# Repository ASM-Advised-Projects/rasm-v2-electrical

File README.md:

Repository for all RASM electronics files. This is mainly comprised of schematics, printed circuit boards, and some custom component libraries.

The images folder which will contain screenshots of the current schematics and boards so that you don't have to have eagle just to get an overview of everything.

Resources for starting to learn how to use Eagle:
* http://eagle.autodesk.com/eagle/documentation
* https://www.autodesk.com/products/eagle/blog/?s=library
* general internetz

Some other tools:
* Trace width calculator: http://circuitcalculator.com/wordpress/?p=25/
* Via dimensions calculator: http://circuitcalculator.com/wordpress/2006/03/12/pcb-via-calculator/

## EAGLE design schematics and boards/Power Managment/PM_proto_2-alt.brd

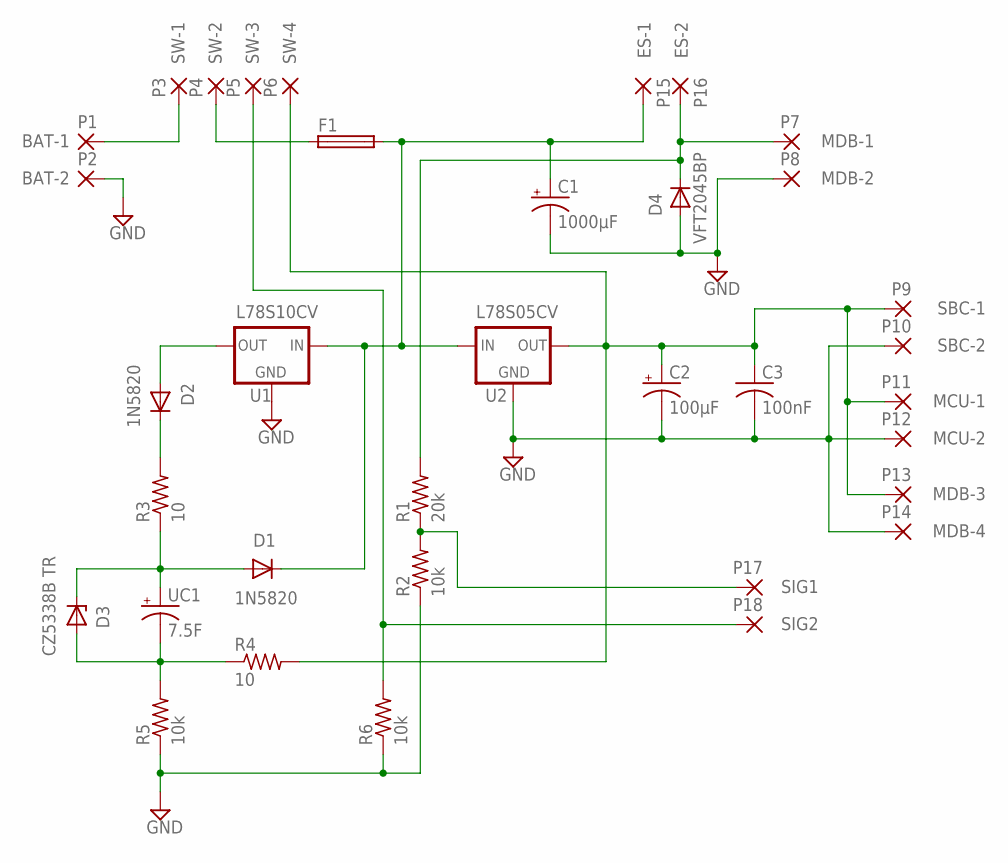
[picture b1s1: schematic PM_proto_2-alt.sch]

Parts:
C1: 1000μF; E7,5-16
C2: 100μF; E2,5-6E
C3: 100nF; C050-024X044
D1, D2: 1N5820; DO41-10
D3: CZ5338B TR; DO41Z10
D4: VFT2045BP
F1: 0297015FUSE; 0297015HOLDER
P1: BAT-1; 1,6/0,8
P2: BAT-2; 1,6/0,8
P3: SW-1; 1,6/0,8
P4: SW-2; 1,6/0,8
P5: SW-3; 1,6/0,8
P6: SW-4; 1,6/0,8
P7: MDB-1; 1,6/0,8
P8: MDB-2; 1,6/0,8
P9: SBC-1; 1,6/0,8
P10: SBC-2; 1,6/0,8
P11: MCU-1; 1,6/0,8
P12: MCU-2; 1,6/0,8
P13: MDB-3; 1,6/0,8
P14: MDB-4; 1,6/0,8
P15: ES-1; 1,6/0,8
P16: ES-2; 1,6/0,8
P17: SIG1; 1,6/0,8
P18: SIG2; 1,6/0,8
R1: 20k; 0204/7
R2, R5, R6: 10k; 0204/7
R3, R4: 10; TNP10SC10R0FE
U1: L78S10CV; 78XXS
U2: L78S05CV; 78XXS
UC1: 7.5F; SCMT32D755MRBB0

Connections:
5VPWR: C2.+, C3.1, P6.1, P9.1, P11.1, P13.1, R4.2, U2.OUT
BATT_1: P1.1, P3.1
BATT_2: F1.1, F1.2 (1), P4.1
BATT_3: C1.+, D1.C, F1.3 (2), F1.4 (2), P15.1, U1.IN, U2.IN
BATT_4: D4.1 (C), P7.1, P16.1, R1.2
CAP_NEG: D3.A, R4.1, R5.2, UC1.2 (-)
CAP_POS: D1.A, D3.C, R3.1, UC1.1 (+)
GND: C1.-, C2.-, C3.2, D4.2 (A), P2.1, P8.1, P10.1, P12.1, P14.1, R2.1, R5.1, R6.1, U1.GND, U2.GND
unnamed: D2.A, U1.OUT
unnamed: D2.C, R3.2
ON_SENSE: P5.1, P18.1, R6.2
V_SENSE: P17.1, R1.1, R2.2

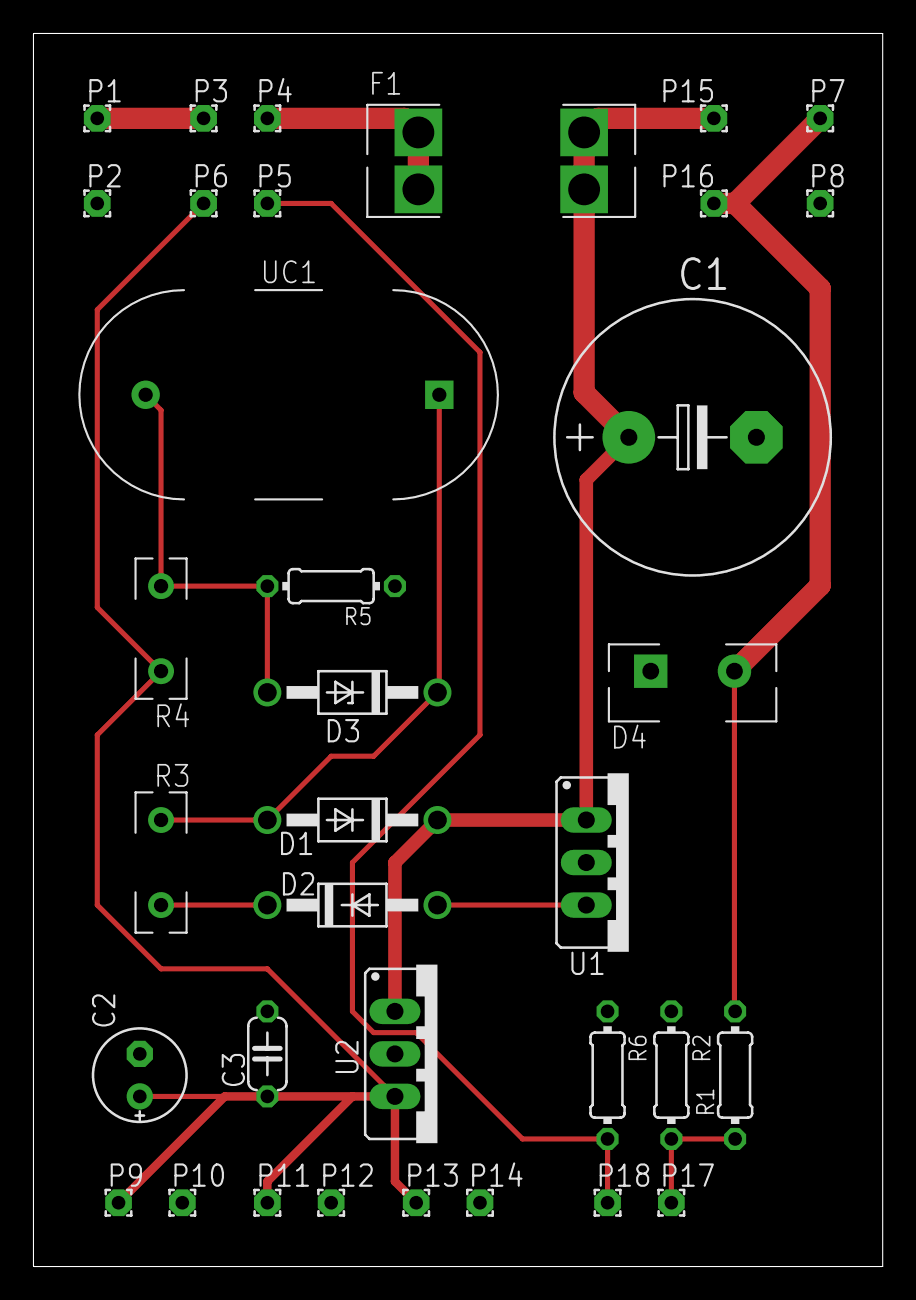
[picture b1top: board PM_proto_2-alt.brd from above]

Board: 2 copper layers, 50.7 x 73.7 mm, 35 parts (0 on the bottom side), 12 nets.

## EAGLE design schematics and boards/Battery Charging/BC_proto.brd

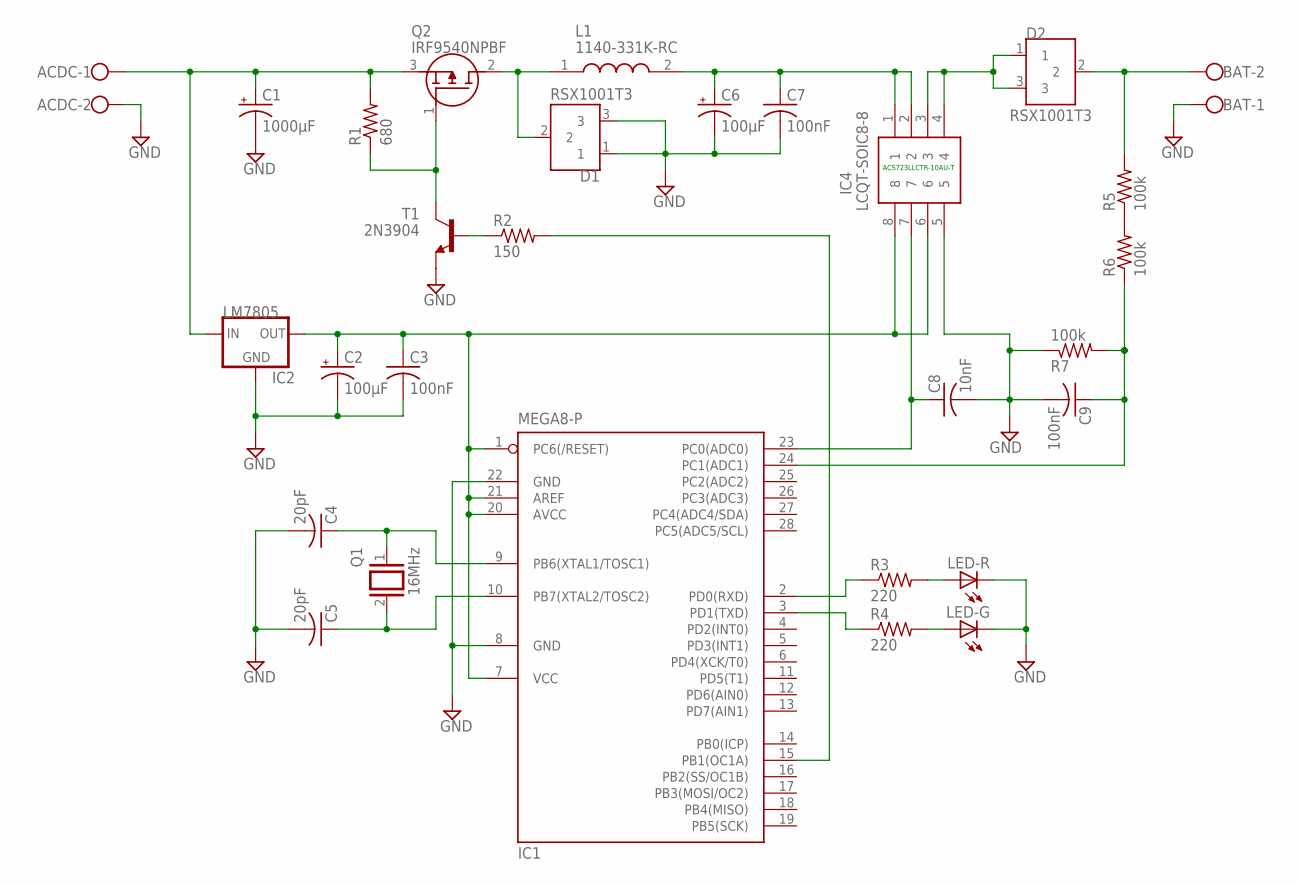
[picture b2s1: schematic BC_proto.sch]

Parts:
ACDC: W237-102
BAT: W237-102
C1: 1000μF; E7,5-16
C2, C6: 100μF; E2,5-6E
C3, C7, C9: 100nF; C050-024X044
C4, C5: 20pF; C050-024X044
C8: 10nF; C050-024X044
D1, D2: RSX1001T3
IC1: MEGA8-P; DIL28-3
IC2: LM7805; 78XXS
IC4: LCQT-SOIC8-8; DIPS762W46P254L1016H160Q8N
L1: 1140-331K-RC
LED-G: TLLR4400; LED3MM
LED-R: TLLR4400; LED3MM
Q1: 16MHz; QS
Q2: IRF9540NPBF; TO254P469X1042X1967-3P
R1: 680; 0204/7
R2: 150; 0204/7
R3, R4: 220; 0204/7
R5, R6, R7: 100k; 0204/7
T1: 2N3904; TO92

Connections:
BUCK_OUT1: C6.+, C7.1, IC4.1, IC4.2, L1.2
BUCK_OUT2: D2.1, D2.3, IC4.3, IC4.4
BUCK_PWM1: IC1.15 (PB1(OC1A)), R2.2
BUCK_PWM2: Q2.1 (G), R1.1, T1.1 (C)
C_SENSE: C8.1, IC1.23 (PC0(ADC0)), IC4.7
GND: ACDC.2, BAT.1, C1.-, C2.-, C3.2, C4.2, C5.2, C6.-, C7.2, C8.2, C9.2, D1.1, D1.3, IC1.8 (GND), IC1.22 (GND), IC2.GND, IC4.5, LED-G.K (C), LED-R.K (C), R7.1, T1.3 (E)
LOGIC_PWR: C2.+, C3.1, IC1.1 (PC6(/RESET)), IC1.7 (VCC), IC1.20 (AVCC), IC1.21 (AREF), IC2.OUT, IC4.6, IC4.8
unnamed: R2.1, T1.2 (B)
unnamed: C4.1, IC1.9 (PB6(XTAL1/TOSC1)), Q1.1
unnamed: C5.1, IC1.10 (PB7(XTAL2/TOSC2)), Q1.2
unnamed: IC1.2 (PD0(RXD)), R3.1
unnamed: IC1.3 (PD1(TXD)), R4.1
unnamed: LED-R.A, R3.2
unnamed: LED-G.A, R4.2
unnamed: R5.1, R6.2
unnamed: D1.2, L1.1, Q2.2 (D)
PWR_IN: ACDC.1, C1.+, IC2.IN, Q2.3 (S), R1.2
PWR_OUT: BAT.2, D2.2, R5.2
V_SENSE: C9.1, IC1.24 (PC1(ADC1)), R6.1, R7.2

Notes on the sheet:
ACS723LLCTR-10AU-T

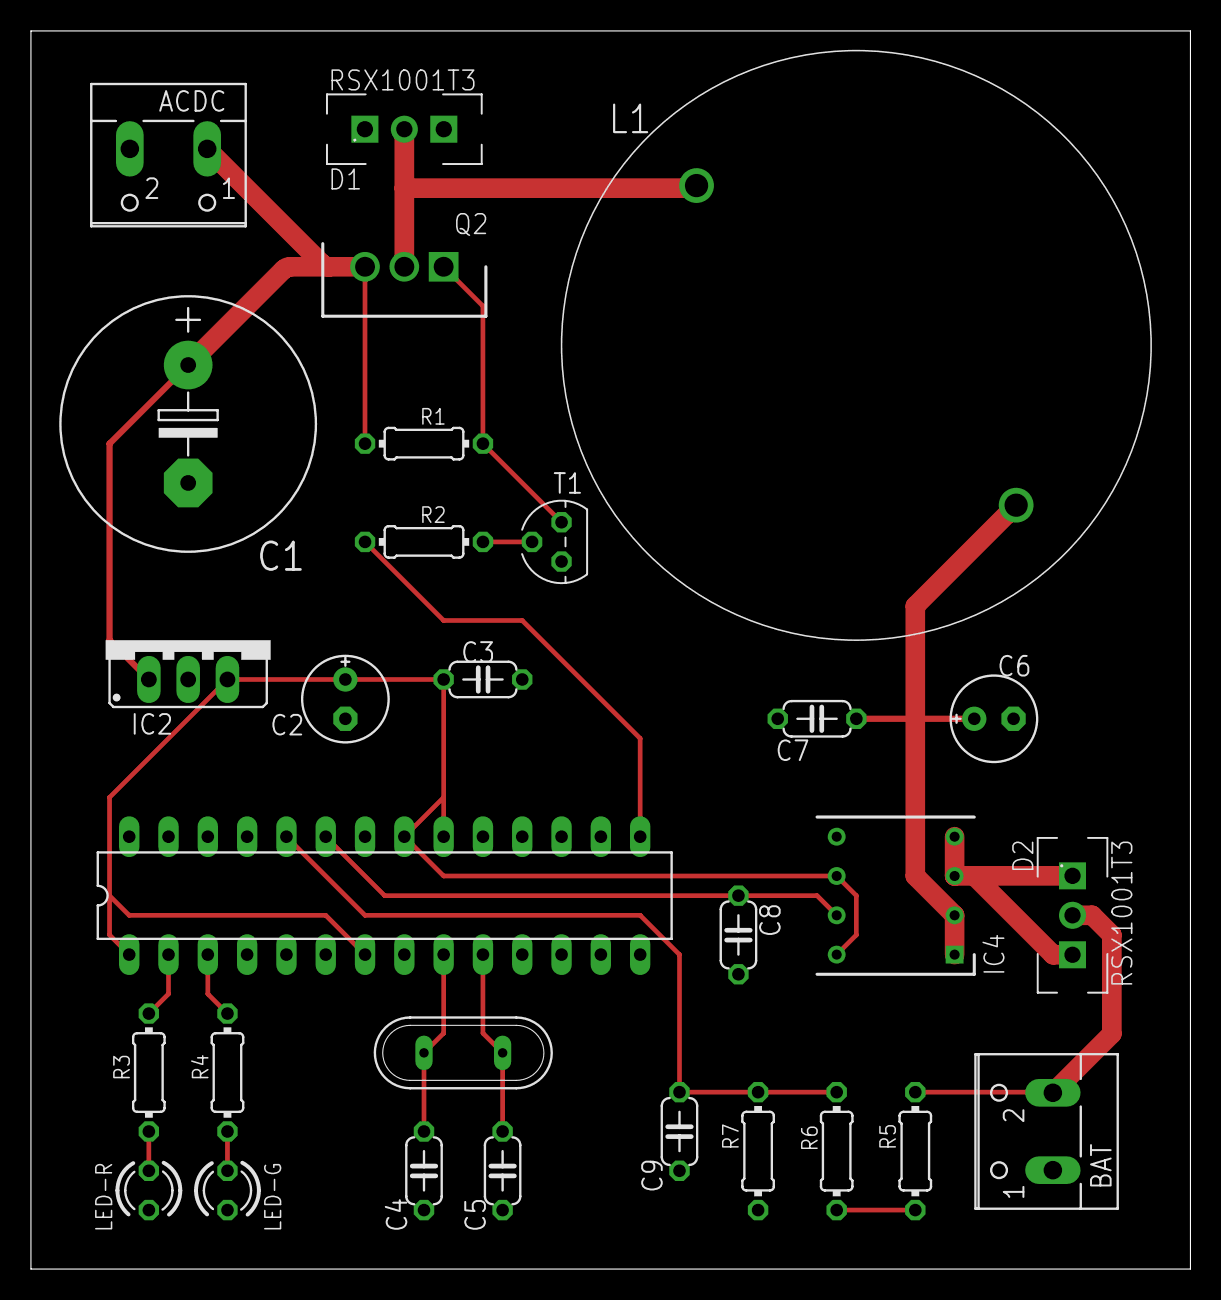
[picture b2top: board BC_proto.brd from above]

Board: 2 copper layers, 74.9 x 80.0 mm, 29 parts (0 on the bottom side), 19 nets.

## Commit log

2018-09-07 Updated the README and added some images.
2018-09-08 Made a small change in the Power Distribution board within the new 5th version. Cleaned up the schematic names and got rid of outdated or useless schematic and board files.
2018-09-08 Added a todo file.
